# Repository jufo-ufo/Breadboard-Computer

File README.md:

# Breadboard-Computer
Let's build a computer from ICs!

## TODO
- [X] Test out NAND vs NOT, AND, OR
- [X] Write specification for V0.4
  - [X] Add Instructionset to "Handbuch"
  - [X] Rework Interrupts
  - [X] I/O specification
  - [X] Update Flags
  - [X] ~~Insert test results~~
- [X] Get familiar with ~~EAGLE/Target3001~~ Kicad/Logisim
- [ ] Build circuit designs

| Part                  | Logic | Schematic | Layout | Breadboard | Etching | Soldering | Etcher | Documenation | Comment
|-----------------------|-------|-----------|--------|------------|---------|-----------|--------|--------------|---------
| Bank                  | [X]   | [X]       | [ ]    | [ ]        | [ ]     | [ ]       |        | [ ]          | 
| Bank\_controller      | [X]   | [X]       | [ ]    | [ ]        | [ ]     | [ ]       |        | [ ]          |
| Memory                | [X]   | [X]       | [X]    | [ ]        | [ ]     | [ ]       |        | [ ]          | 
| Register\_File        | [X]   | [X]       | [ ]    | [ ]        | [ ]     | [ ]       |        | [ ]          | 
| ALU                   | [X]   | [X]       | [ ]    | [ ]        | [ ]     | [ ]       |        | [ ]          | 
| IV\_Storage           | [X]   | [ ]       | [ ]    | [ ]        | [ ]     | [ ]       |        | [ ]          | 
| Interrupt\_Controller | [ ]   | [ ]       | [ ]    | [ ]        | [ ]     | [ ]       |        | [ ]          | 
| Timer                 | [X]   | [ ]       | [ ]    | [ ]        | [ ]     | [ ]       |        | [ ]          | 
| Freq\_Counter         | [X]   | [ ]       | [ ]    | [ ]        | [ ]     | [ ]       |        | [ ]          | 
| Instruction\_Decoder  | [X]   | [ ]       | [ ]    | [ ]        | [ ]     | [ ]       |        | [ ]          | 
| IO\_Controller        | [ ]   | [ ]       | [ ]    | [ ]        | [ ]     | [ ]       |        | [ ]          | 
| Activation\_Module    | [X]   | [X]       | [X]    | [X]        | [ ] x7  | [ ] x7    |        | [ ]          | 
| Dual\_Register        | [X]   | [X]       | [X]    | [X]        | [ ] x2  | [ ] x2    |        | [ ]          | Replacement for BID-Regiser and IR
https://www.youtube.com/watch?v=9aUsTlBjspE

## TODO for Presentation
| Module               | Logic | Schematic | Layout | Breaboard | DIY Etching | Soldering | Comment
|----------------------|-------|-----------|--------|-----------|-------------|-----------|--------
| Activation Module x4 | [X]   | [X]       | [X]    |           |             | [ ]       |
| Register File        | [X]   | [X]       | [ ]    |           |             | [ ]       |
| ALU                  | [X]   | [ ]       |        | [ ]       |             |           |
| Dual Register        | [X]   | [X]       | [X]    |           | [X]         | [ ]       |
| Memory               | [X]   | [X]       | [X]    |           |             | [ ]       |
| Instruction Decoader | [X]   |           |        | [ ]       |             |           | No Schematic need, due unstable design
| IO-Controller        | [X]   |           |        | [ ]       |             |           | No Schematic need, has to be build spontainiously

## Was macht unseren Computer besonders?

- Modular: Die Funktionialiät des Computer kann erweitern werden indem neues einfach eingesteckt wird
- 2 Bus-Architektur: Efficenter
- IO-System sehr vielfältig: bis zu 2^16 IO-Geräte
- Wäre der Laufzeit anpassbares Instruktions Satz (kommt noch)
- Keine Softwareverwaltes Berechtigungs System: Supervisor/Usermode

=> Sehr einfache Anpassbarkeit und Optimierung auf Verschieden Zenarien

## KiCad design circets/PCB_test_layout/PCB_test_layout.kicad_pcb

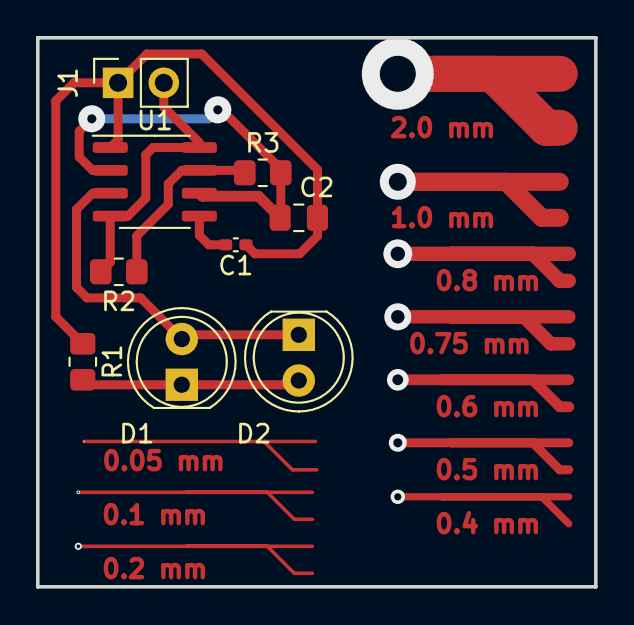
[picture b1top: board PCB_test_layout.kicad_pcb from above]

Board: 2 copper layers, 31.0 x 30.5 mm, 9 parts (0 on the bottom side), 7 nets.

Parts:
C1: 10n; C_0402_1005Metric_Pad0.74x0.62mm_HandSolder
C2: 10µ; C_0805_2012Metric_Pad1.18x1.45mm_HandSolder
D1, D2: LED; LED_D5.0mm
J1: Conn_01x02_Male; PinSocket_1x02_P2.54mm_Vertical
R1: 220; R_0805_2012Metric_Pad1.20x1.40mm_HandSolder
R2: 40k; R_0805_2012Metric_Pad1.20x1.40mm_HandSolder
R3: 10k; R_0805_2012Metric_Pad1.20x1.40mm_HandSolder
U1: NE555D; SOIC-8_3.9x4.9mm_P1.27mm

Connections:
+5V: J1.2, R2.2, U1.4 (R), U1.8 (VCC)
GND: C1.1, C2.2, J1.1, R1.1, U1.1 (GND)
unnamed: C1.2, U1.5 (CV)
unnamed: C2.1, R3.2, U1.2 (TR), U1.6 (THR)
unnamed: D1.1 (K), D2.2 (A), R1.2
unnamed: D1.2 (A), D2.1 (K), U1.3 (Q)
unnamed: R2.1, R3.1, U1.7 (DIS)

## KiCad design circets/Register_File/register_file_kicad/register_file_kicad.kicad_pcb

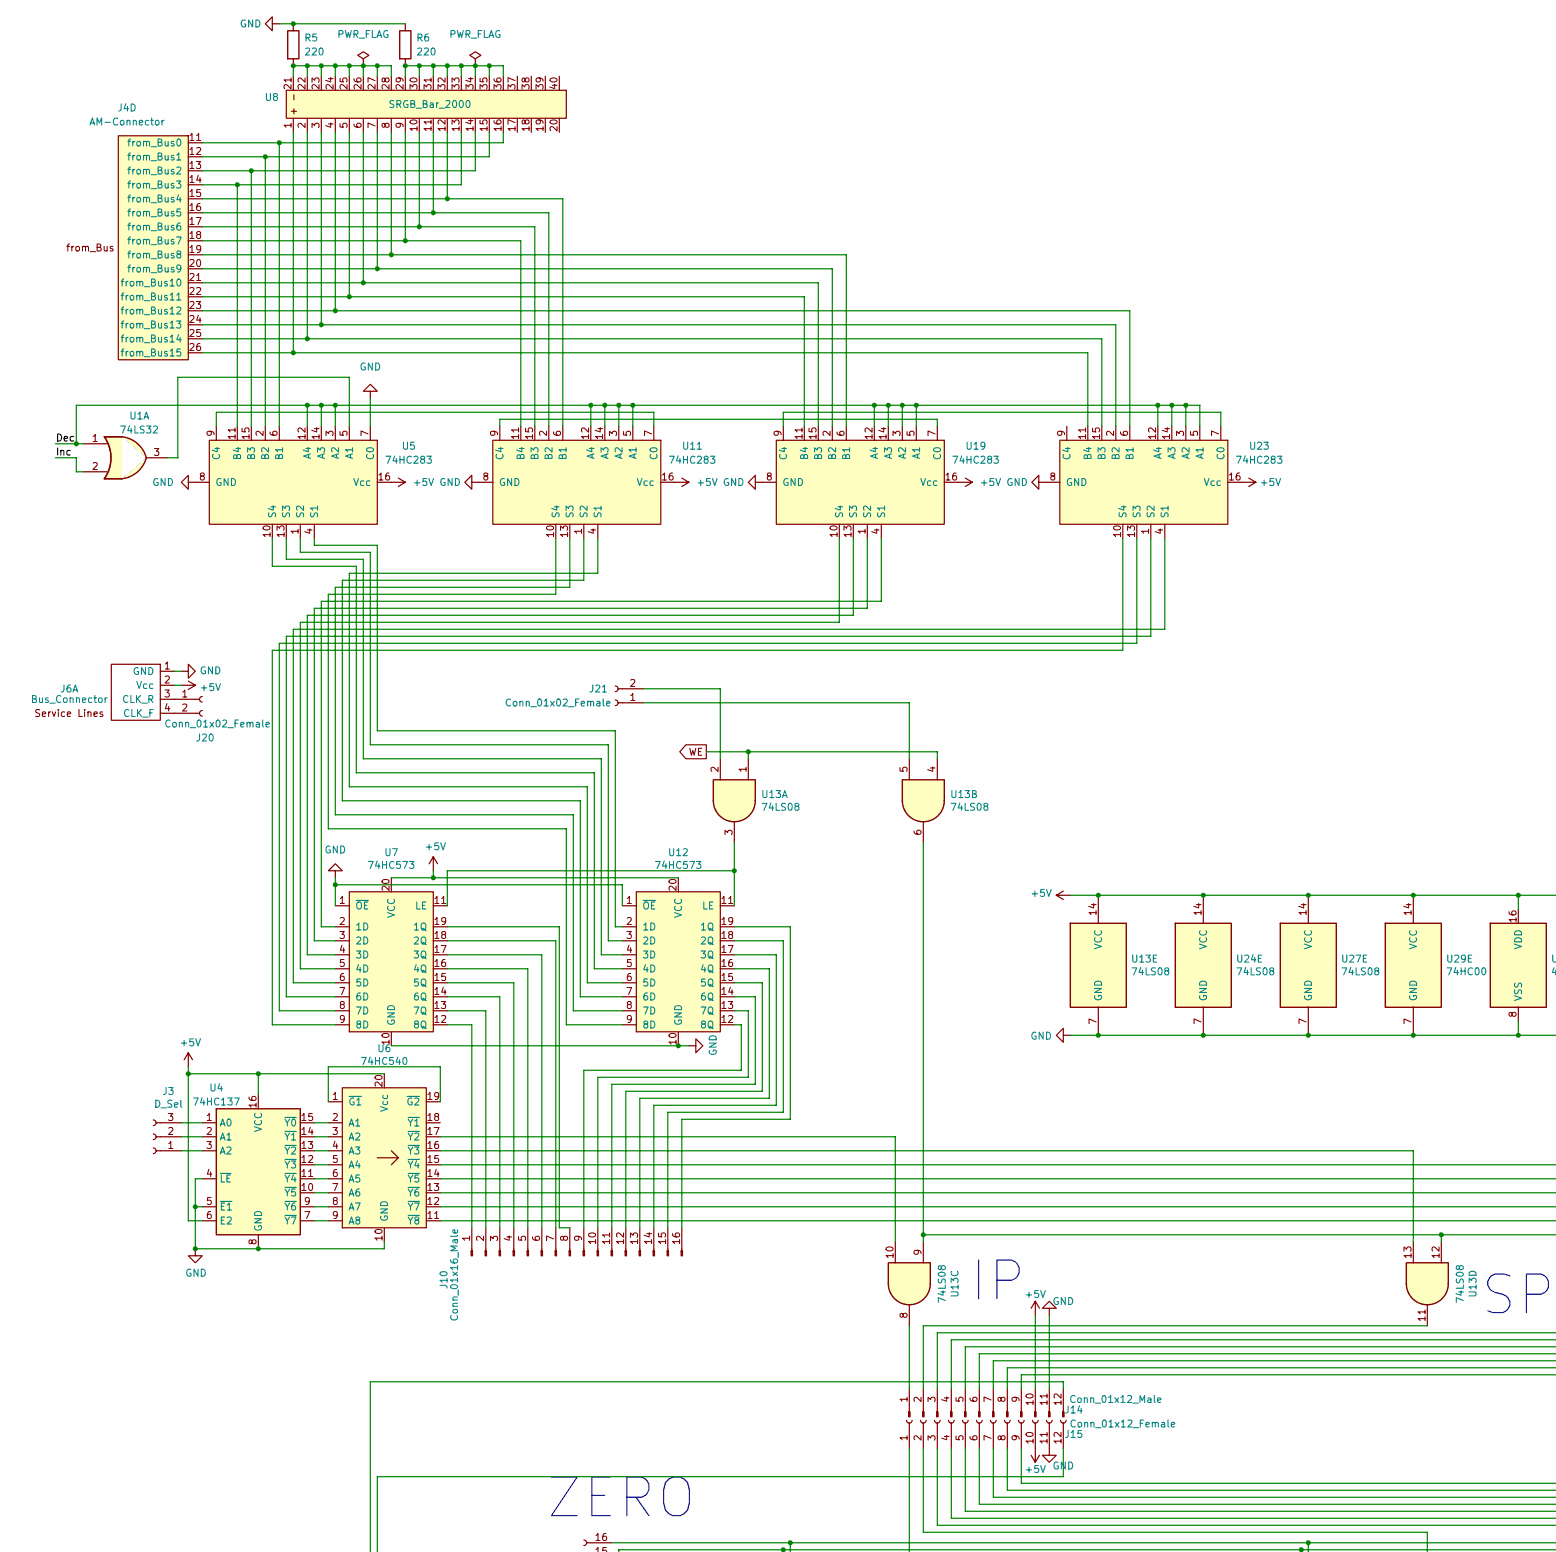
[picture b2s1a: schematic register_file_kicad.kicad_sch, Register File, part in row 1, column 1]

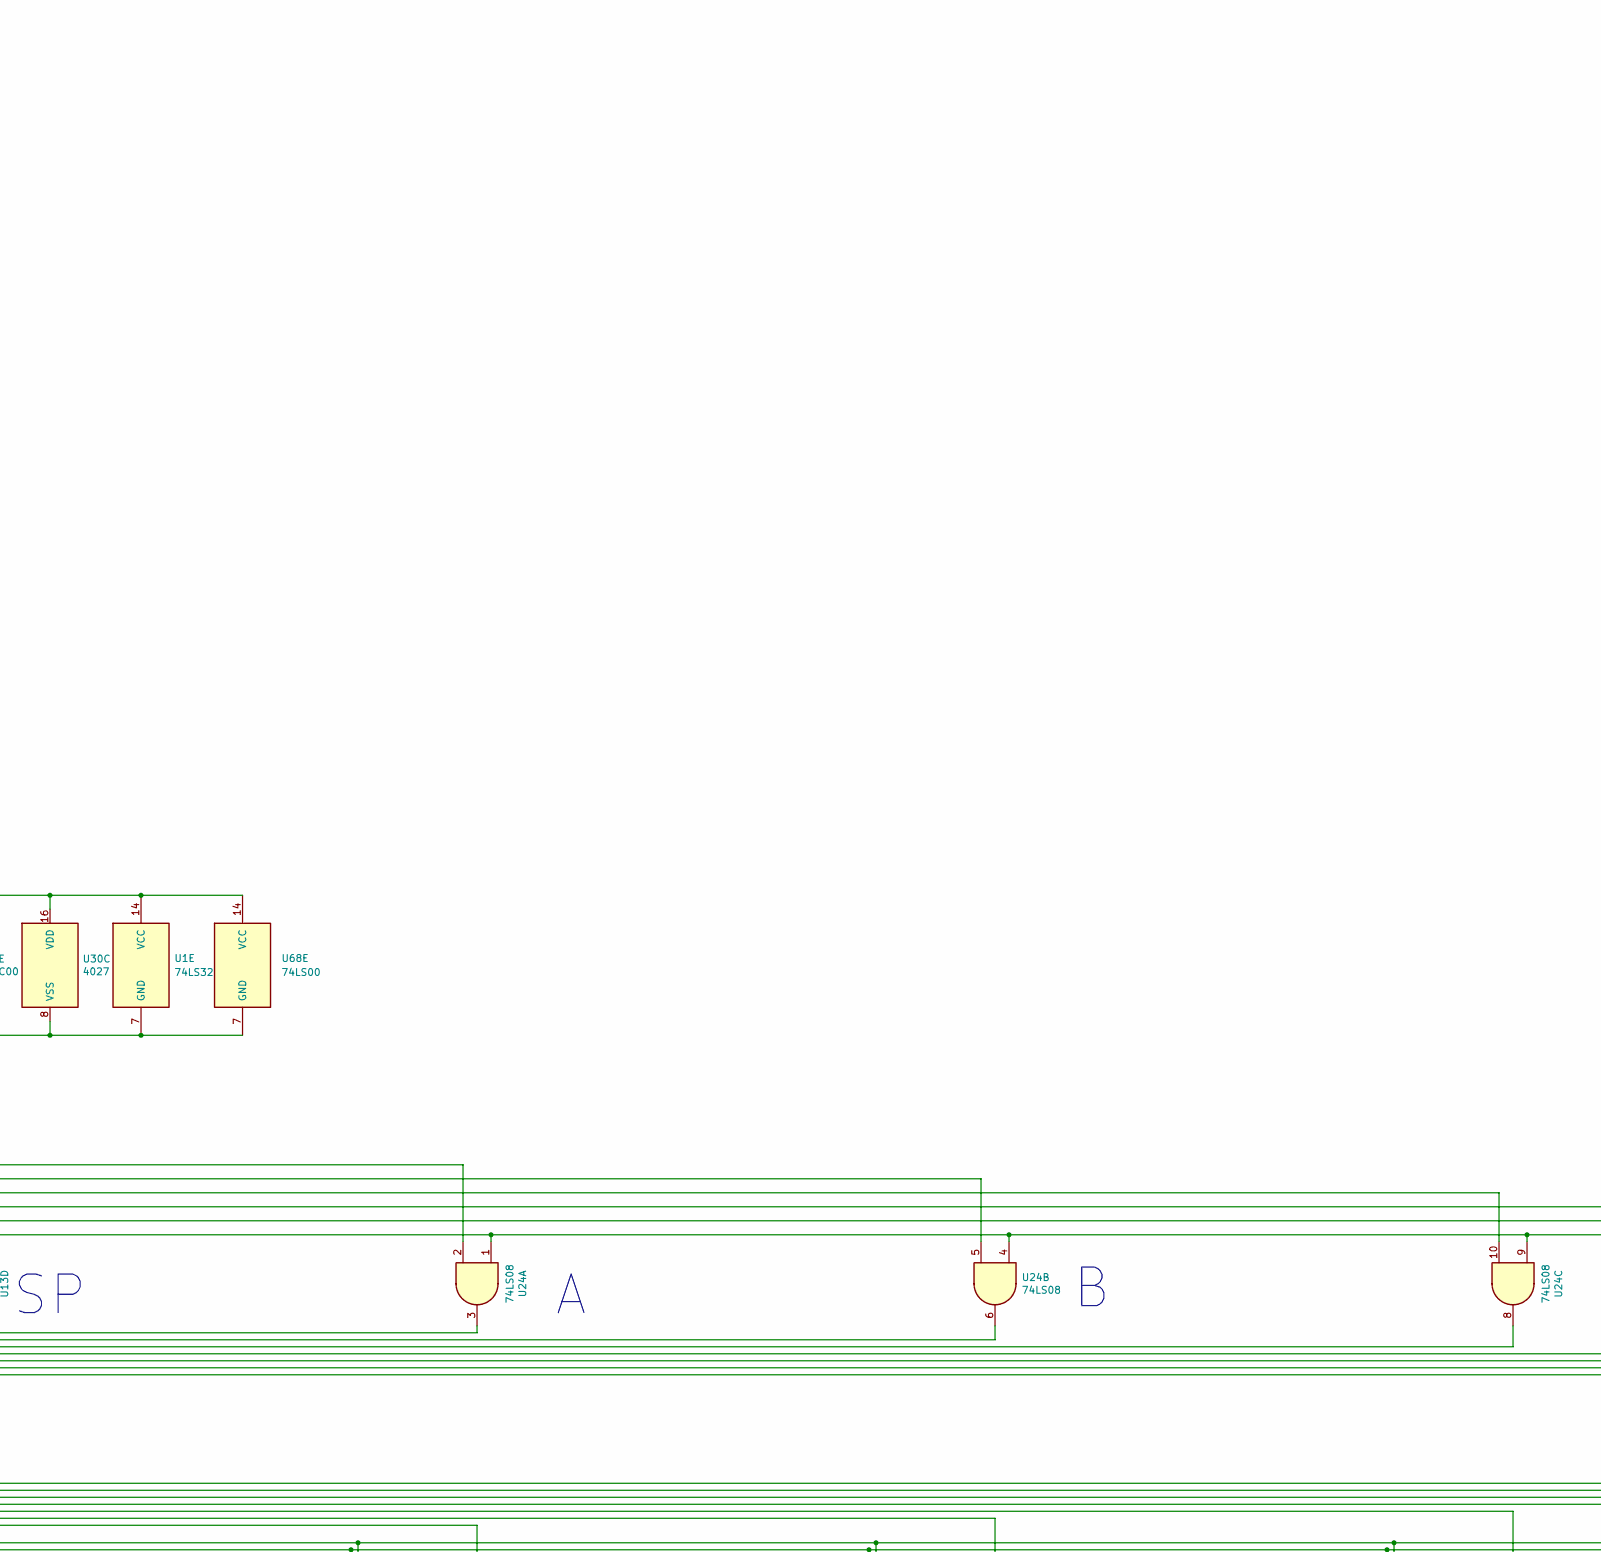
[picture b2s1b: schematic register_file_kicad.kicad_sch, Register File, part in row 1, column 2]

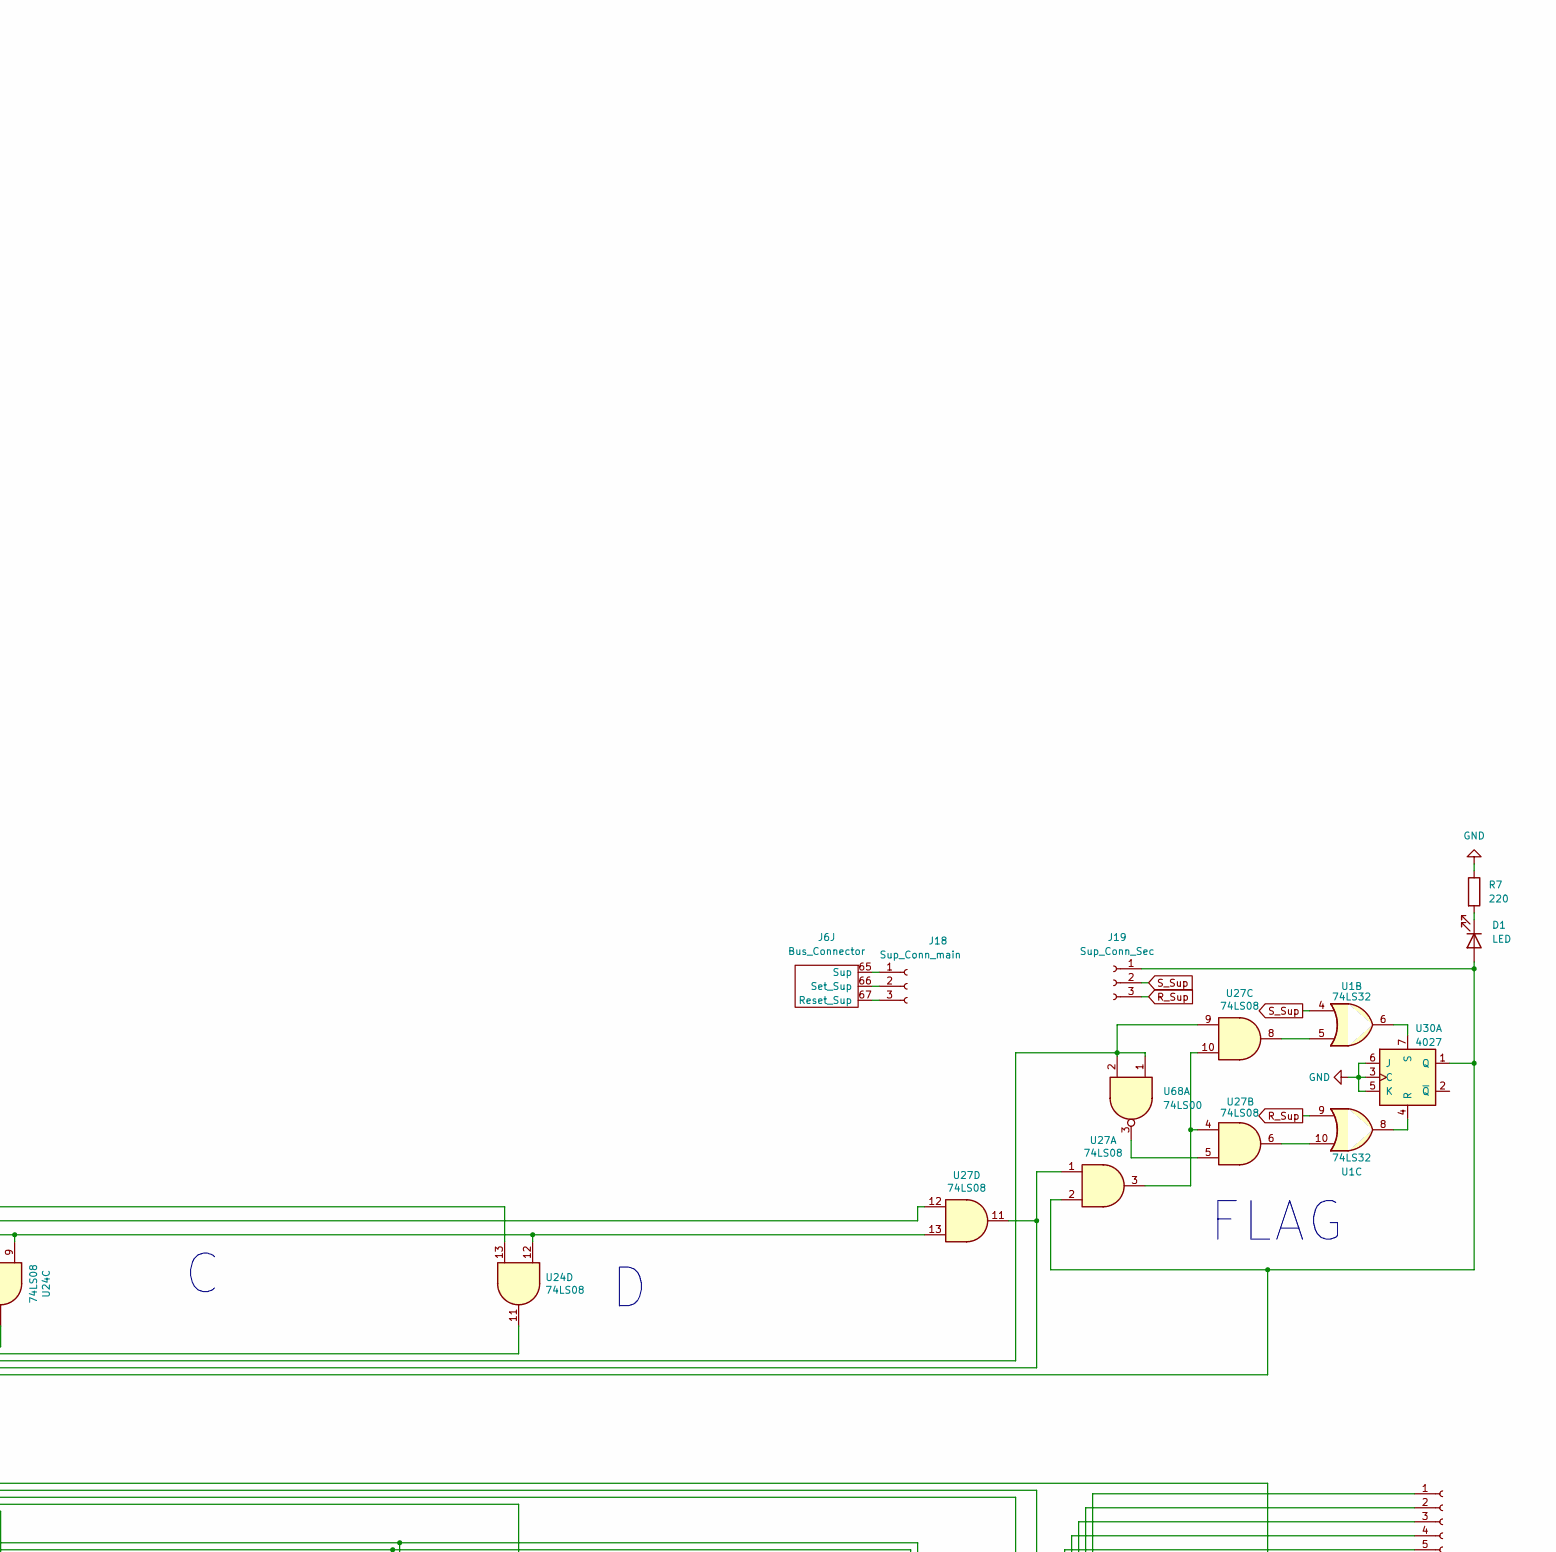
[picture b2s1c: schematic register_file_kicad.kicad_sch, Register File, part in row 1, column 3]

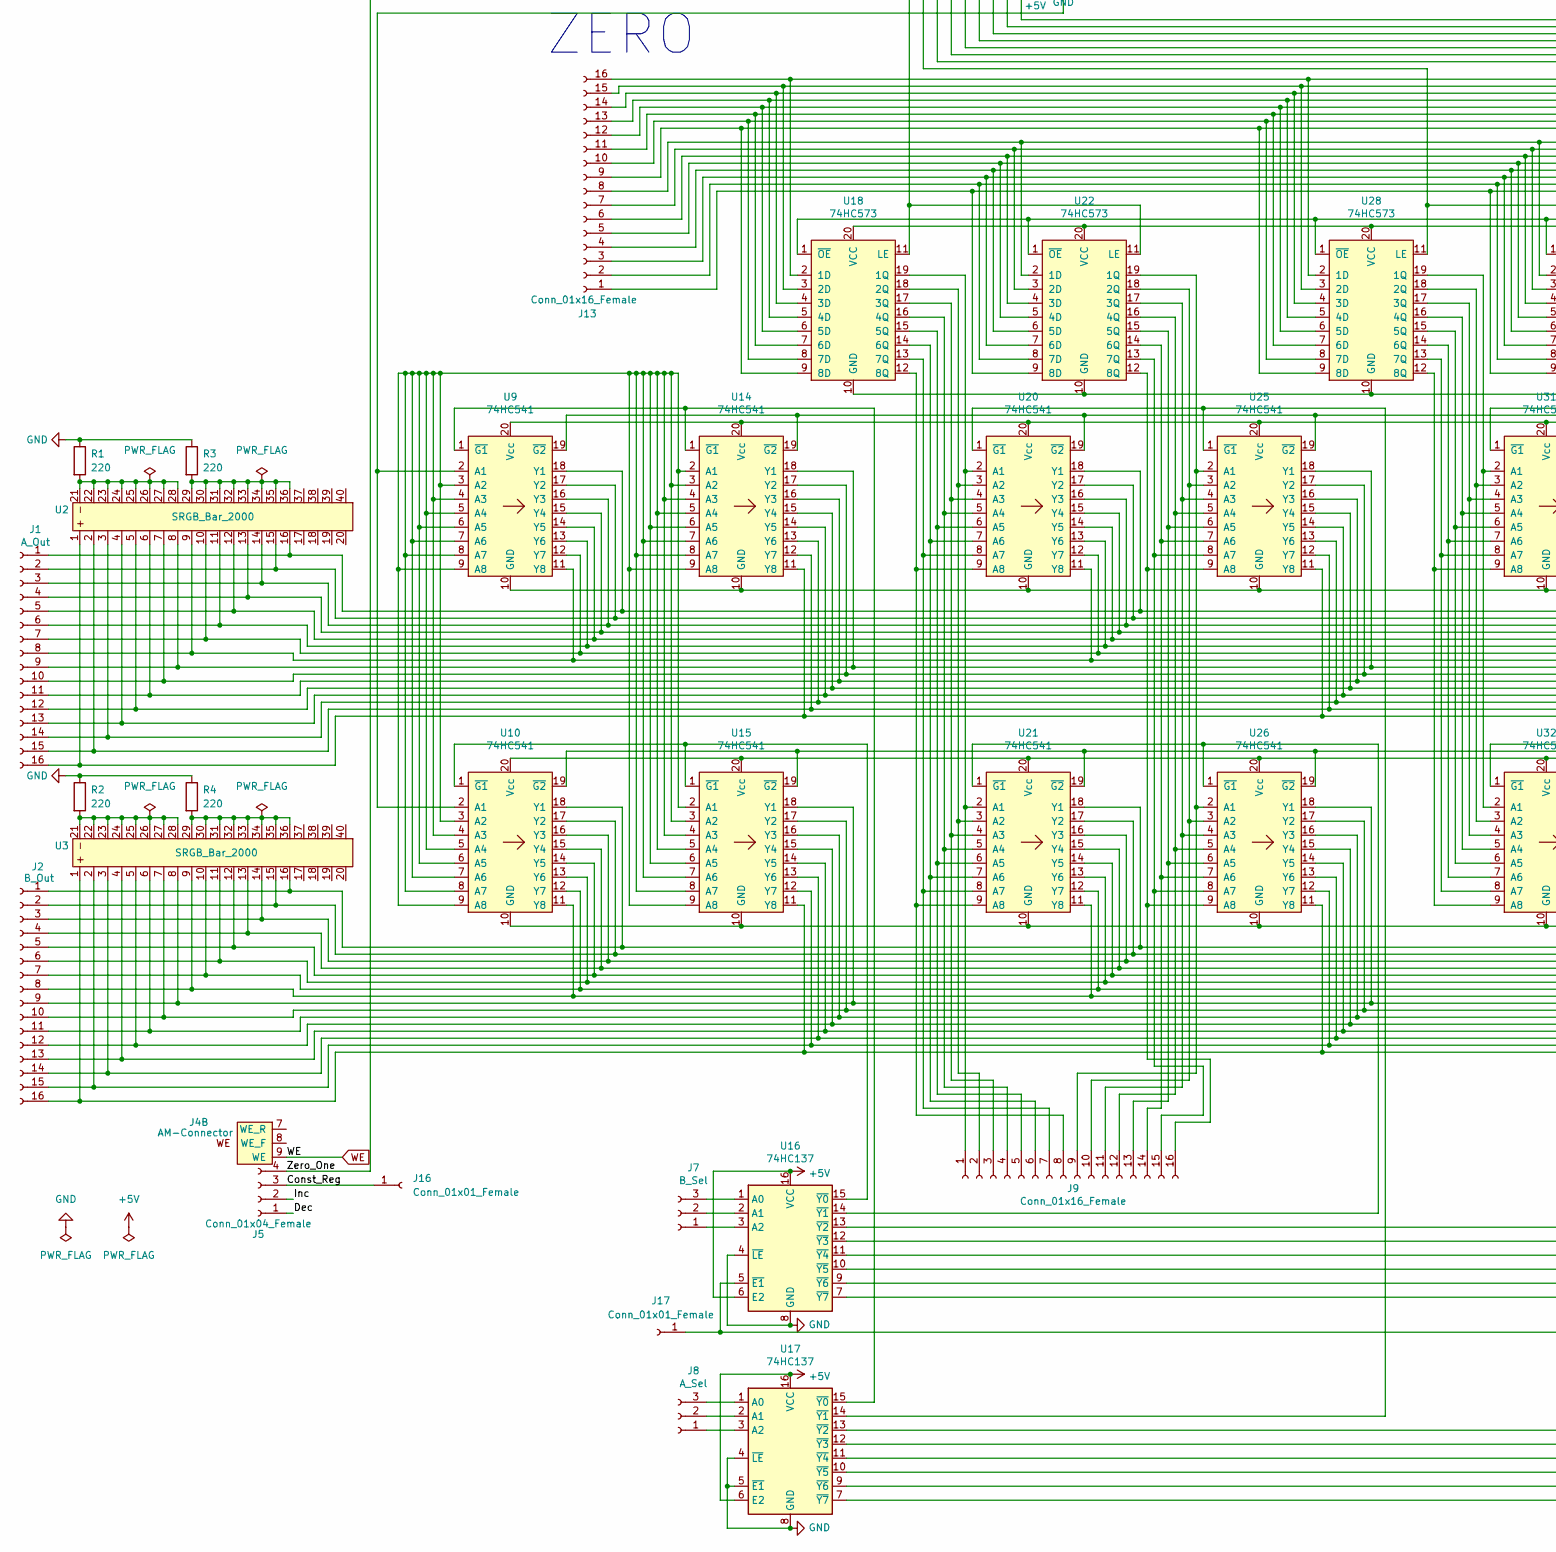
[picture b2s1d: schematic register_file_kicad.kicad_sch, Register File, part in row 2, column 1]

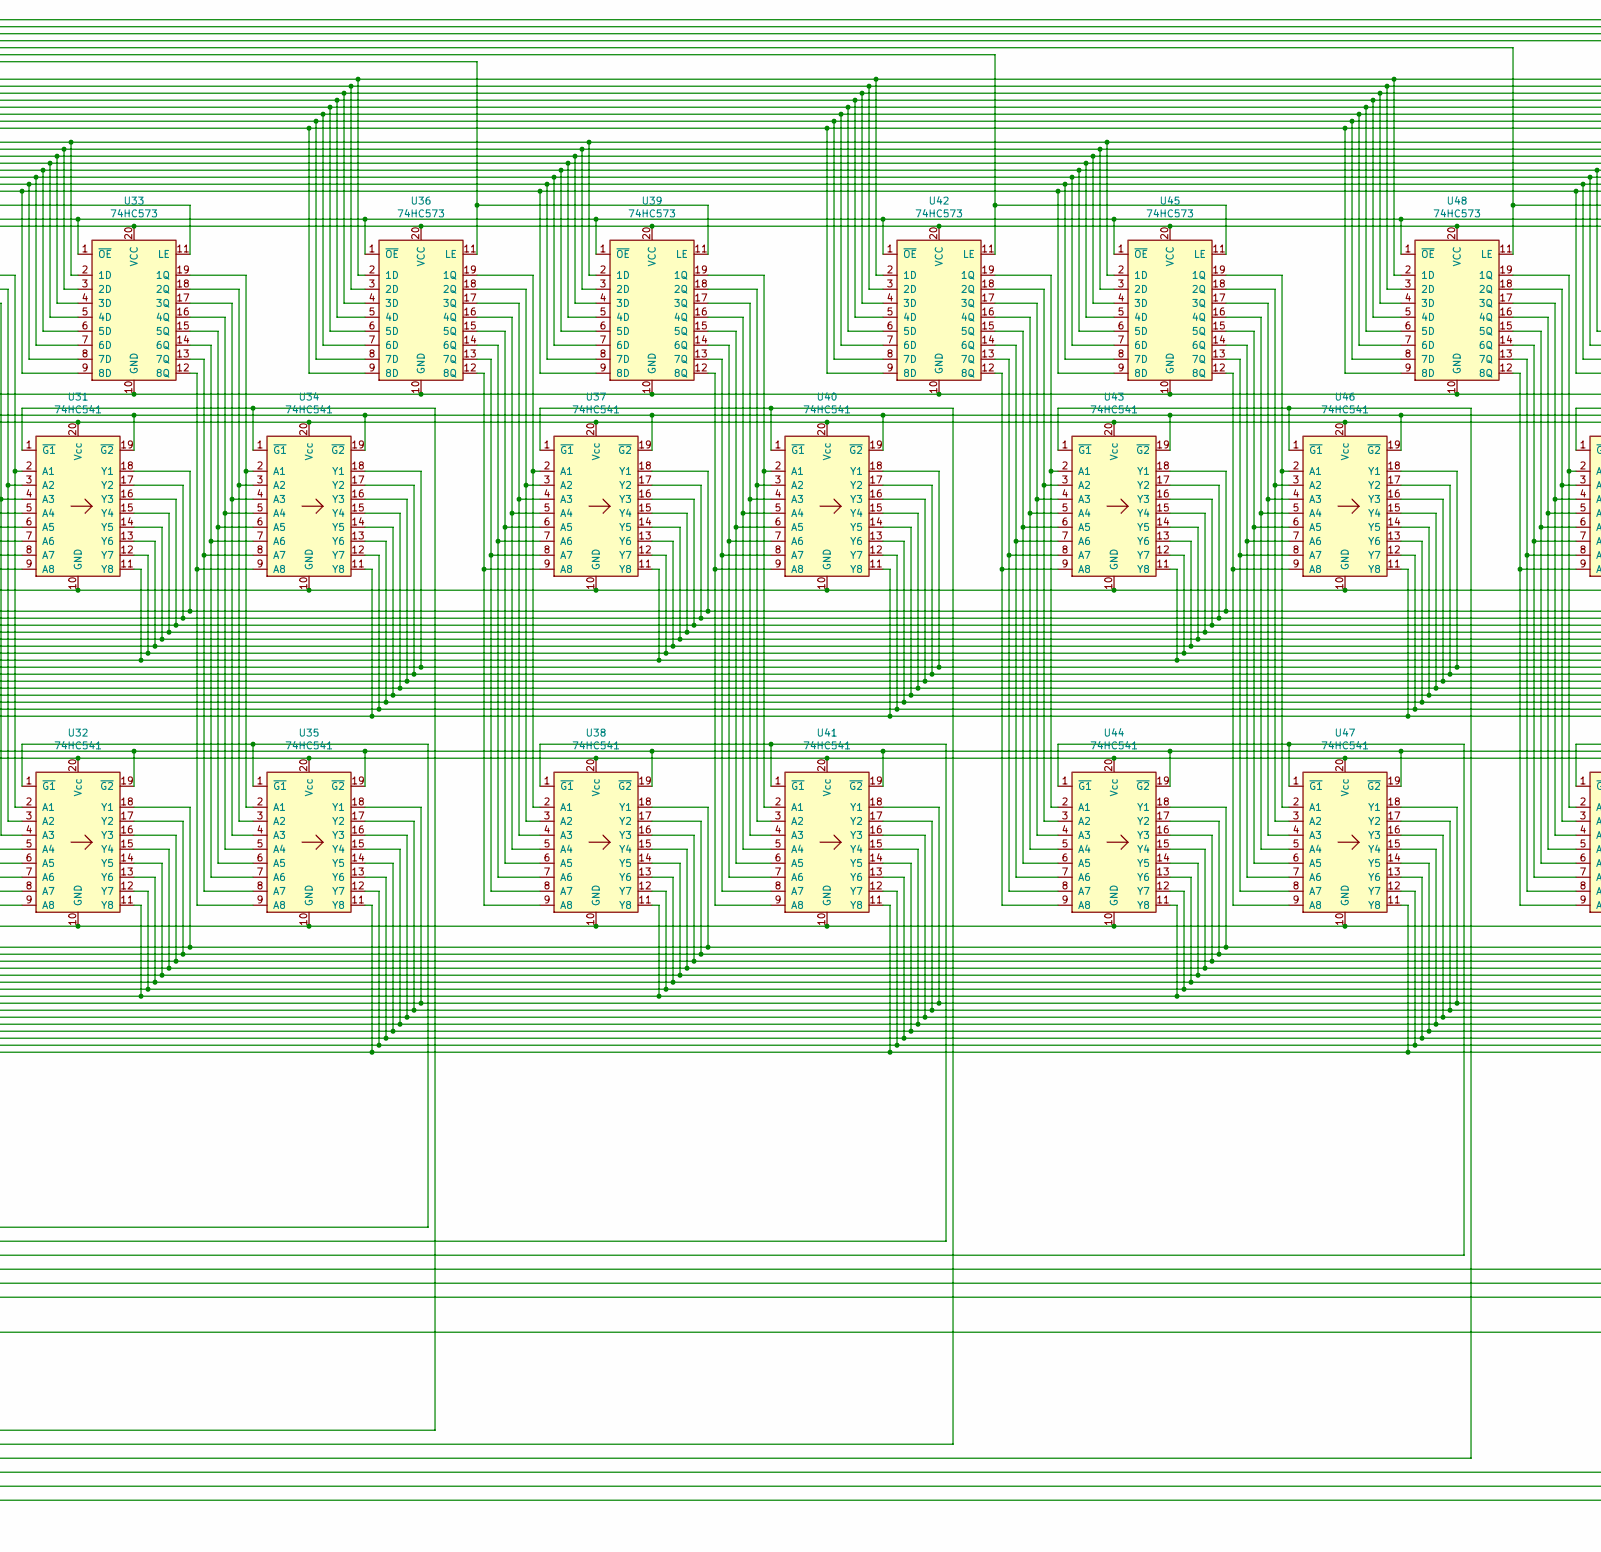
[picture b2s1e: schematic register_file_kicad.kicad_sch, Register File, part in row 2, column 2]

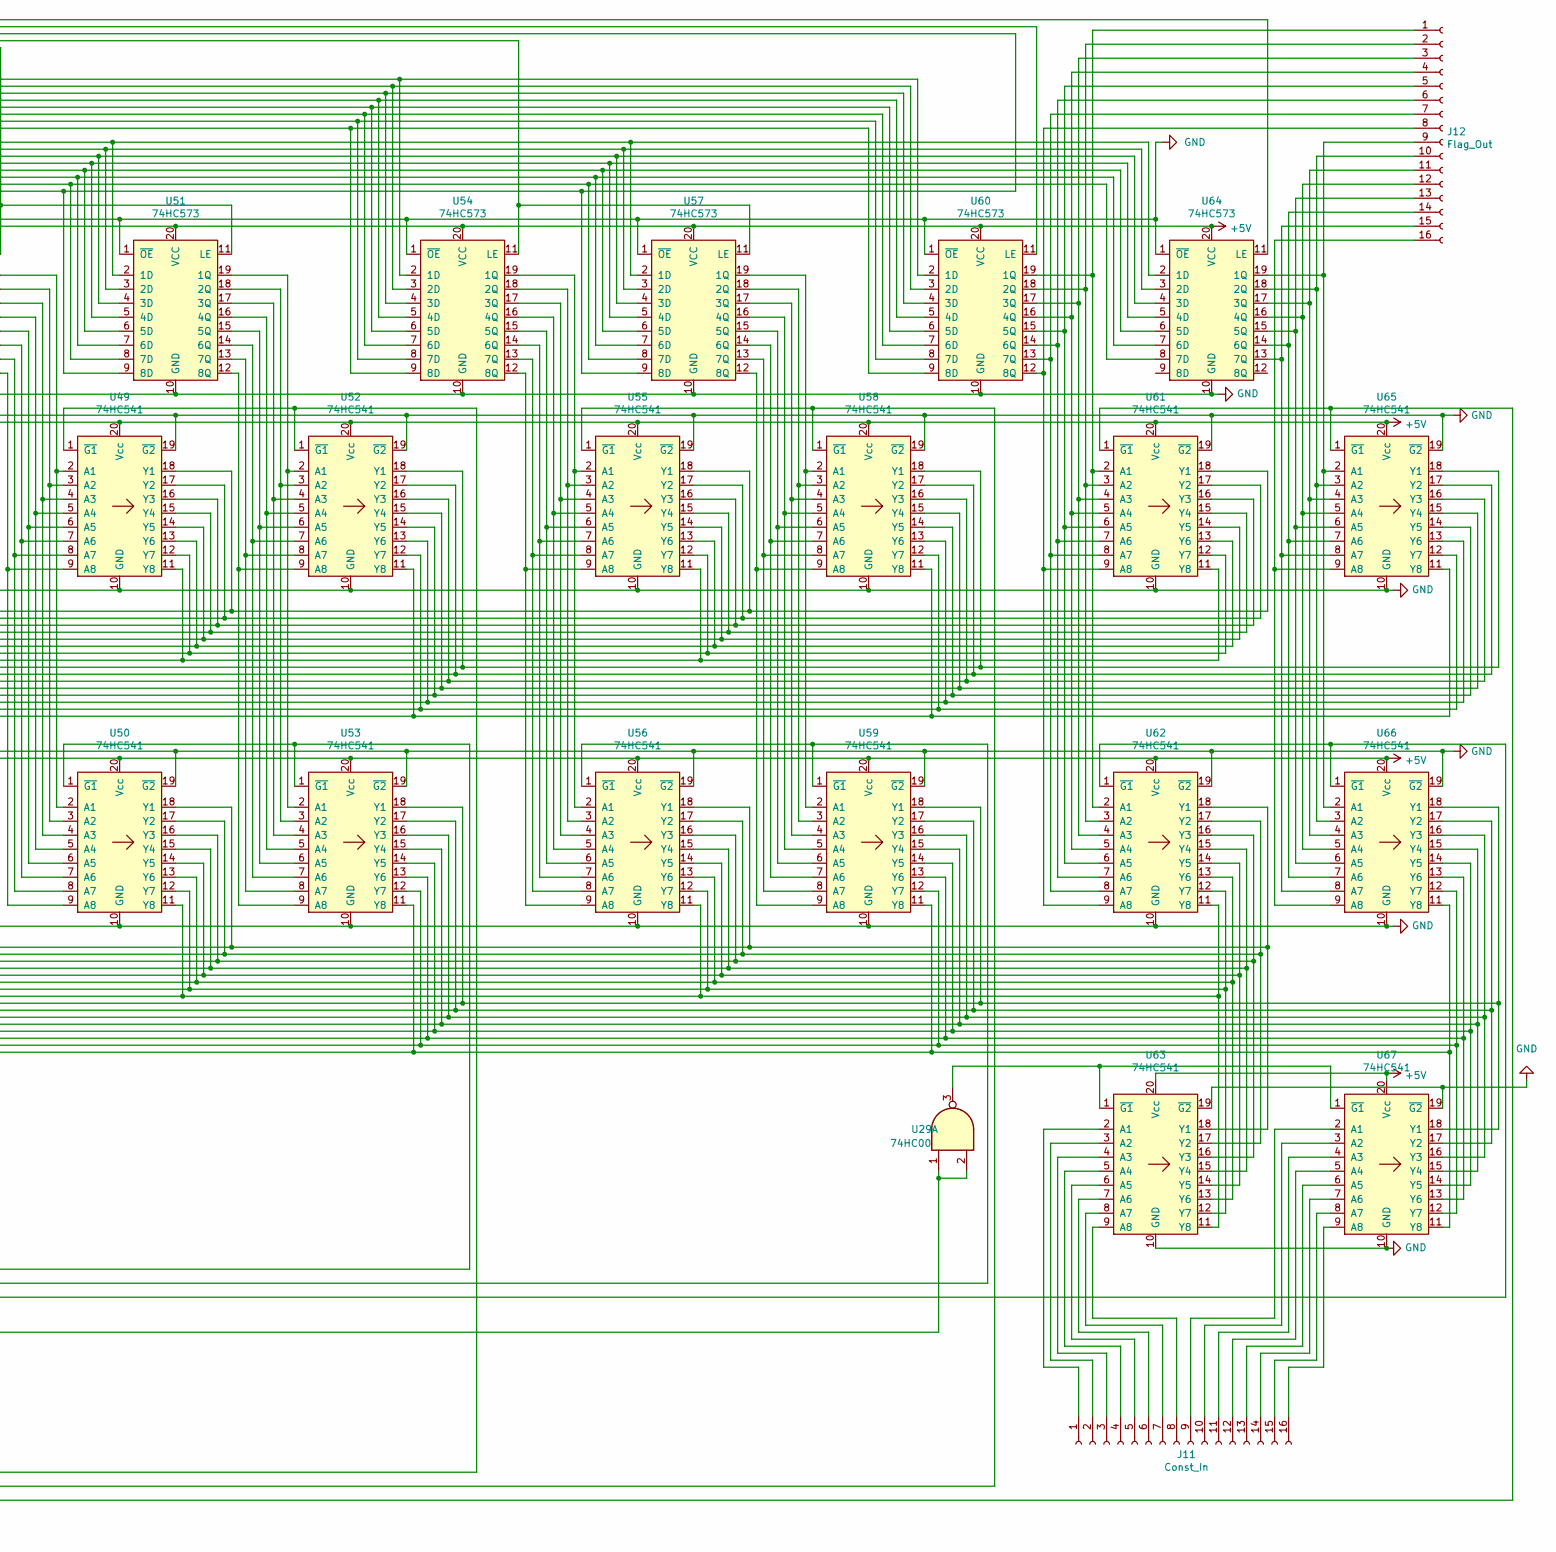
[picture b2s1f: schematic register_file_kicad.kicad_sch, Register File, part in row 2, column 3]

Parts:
D1: LED; LED_D5.0mm
J1: A_Out; PinHeader_1x16_P2.54mm_Vertical
J2: B_Out; PinHeader_1x16_P2.54mm_Vertical
J3: D_Sel; PinSocket_1x03_P2.54mm_Horizontal
J4: AM-Connector; PinHeader_1x42_P2.54mm_Horizontal
J5: Conn_01x04_Female; PinHeader_1x04_P2.54mm_Horizontal
J6: Bus_Connector; PinHeader_1x78_P2.54mm_Horizontal
J7: B_Sel; PinHeader_1x03_P2.54mm_Horizontal
J8: A_Sel; PinHeader_1x03_P2.54mm_Horizontal
J9, J13: Conn_01x16_Female; PinSocket_1x16_P2.54mm_Vertical
J10: Conn_01x16_Male; PinSocket_1x16_P2.54mm_Vertical
J11: Const_In; PinHeader_1x16_P2.54mm_Horizontal
J12: Flag_Out; PinHeader_1x16_P2.54mm_Horizontal
J14: Conn_01x12_Male; PinSocket_1x12_P2.54mm_Vertical
J15: Conn_01x12_Female; PinSocket_1x12_P2.54mm_Vertical
J16, J17: Conn_01x01_Female; PinSocket_1x01_P2.54mm_Vertical
J18: Sup_Conn_main; PinSocket_1x03_P2.54mm_Horizontal
J19: Sup_Conn_Sec; PinSocket_1x03_P2.54mm_Horizontal
J20, J21: Conn_01x02_Female; PinSocket_1x02_P2.54mm_Vertical
R1, R2, R3, R4, R5, R6, R7: 220; R_Axial_DIN0309_L9.0mm_D3.2mm_P5.08mm_Vertical
U1: 74LS32; DIP-14_W7.62mm_Socket
U2, U3, U8: SRGB_Bar_2000; SRGB_2000
U4, U16, U17: 74HC137; DIP-16_W7.62mm_Socket
U5, U11, U19, U23: 74HC283; DIP-16_W7.62mm_Socket
U6: 74HC540; DIP-20_W7.62mm_Socket
U7, U12, U18, U22, U28, U33, U36, U39, U42, U45, U48, U51, U54, U57, U60, U64: 74HC573; DIP-20_W7.62mm_Socket
U9, U10: 74HC541; SO-20_5.3x12.6mm_P1.27mm
U13, U24, U27: 74LS08; DIP-14_W7.62mm_Socket
U14, U15, U20, U21, U25, U26, U31, U32, U34, U35, U37, U38, U40, U41, U43, U44, U46, U47, U49, U50, U52, U53, U55, U56, U58, U59, U61, U62, U63, U65, U66, U67: 74HC541; SO-20_12.8x7.5mm_P1.27mm
U29: 74HC00; DIP-14_W7.62mm_Socket
U30: 4027; DIP-16_W7.62mm_Socket
U68: 74LS00; DIP-14_W7.62mm_Socket

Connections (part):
+5V: J6.2 (Vcc), J14.10, J15.10, U1.14 (VCC), U4.6 (E2), U4.16 (VCC), U5.16 (Vcc), U6.20 (Vcc), U7.20 (VCC), U9.20 (Vcc), U10.20 (Vcc), U11.16 (Vcc), U12.20 (VCC), U13.14 (VCC), U14.20 (Vcc), U15.20 (Vcc), U16.6 (E2), U16.16 (VCC), U17.6 (E2), U17.16 (VCC), U18.20 (VCC), U19.16 (Vcc), U20.20 (Vcc), U21.20 (Vcc), U22.20 (VCC), U23.16 (Vcc), U24.14 (VCC), U25.20 (Vcc), U26.20 (Vcc), U27.14 (VCC), U28.20 (VCC), U29.14 (VCC), U30.16 (VDD), U31.20 (Vcc), U32.20 (Vcc), U33.20 (VCC), U34.20 (Vcc), U35.20 (Vcc), U36.20 (VCC), U37.20 (Vcc), U38.20 (Vcc), U39.20 (VCC), U40.20 (Vcc), U41.20 (Vcc), U42.20 (VCC), U43.20 (Vcc), U44.20 (Vcc), U45.20 (VCC), U46.20 (Vcc), U47.20 (Vcc), U48.20 (VCC), U49.20 (Vcc), U50.20 (Vcc), U51.20 (VCC), U52.20 (Vcc), U53.20 (Vcc), U54.20 (VCC), U55.20 (Vcc), U56.20 (Vcc), U57.20 (VCC), U58.20 (Vcc), U59.20 (Vcc), U60.20 (VCC), U61.20 (Vcc), U62.20 (Vcc), U63.20 (Vcc), U64.20 (VCC), U65.20 (Vcc), U66.20 (Vcc), U67.20 (Vcc), U68.14 (VCC)
/Const_Reg: J5.3, J16.1
/Dec: J5.1, U1.1, U5.3 (A2), U5.12 (A4), U5.14 (A3), U11.3 (A2), U11.5 (A1), U11.12 (A4), U11.14 (A3), U19.3 (A2), U19.5 (A1), U19.12 (A4), U19.14 (A3), U23.3 (A2), U23.5 (A1), U23.12 (A4), U23.14 (A3)
/Inc: J5.2, U1.2
/Zero_One: J5.4, J14.12
GND: J6.1 (GND), J14.11, J15.11, R1.1, R2.1, R3.1, R4.1, R5.1, R6.1, R7.1, U1.7 (GND), U4.4 (~LE), U4.5 (~E1), U4.8 (GND), U5.7 (C0), U5.8 (GND), U6.10 (GND), U7.1 (~OE), U7.10 (GND), U9.10 (GND), U9.19 (~G2), U10.10 (GND), U10.19 (~G2), U11.8 (GND), U12.1 (~OE), U12.10 (GND), U13.7 (GND), U14.10 (GND), U14.19 (~G2), U15.10 (GND), U15.19 (~G2), U16.4 (~LE), U16.8 (GND), U17.4 (~LE), U17.5 (~E1), U17.8 (GND), U18.1 (~OE), U18.10 (GND), U19.8 (GND), U20.10 (GND), U20.19 (~G2), U21.10 (GND), U21.19 (~G2), U22.1 (~OE), U22.10 (GND), U23.8 (GND), U24.7 (GND), U25.10 (GND), U25.19 (~G2), U26.10 (GND), U26.19 (~G2), U27.7 (GND), U28.1 (~OE), U28.10 (GND), U29.7 (GND), U30.3 (C), U30.5 (K), U30.6 (J), U30.8 (VSS), U31.10 (GND), U31.19 (~G2), U32.10 (GND), U32.19 (~G2), U33.1 (~OE), U33.10 (GND), U34.10 (GND), U34.19 (~G2), U35.10 (GND), U35.19 (~G2), U36.1 (~OE), U36.10 (GND), U37.10 (GND), U37.19 (~G2), U38.10 (GND), U38.19 (~G2), U39.1 (~OE), U39.10 (GND), U40.10 (GND), U40.19 (~G2), U41.10 (GND), U41.19 (~G2), U42.1 (~OE), U42.10 (GND), U43.10 (GND), U43.19 (~G2), U44.10 (GND)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
unnamed: D1.1 (K), R7.2
unnamed: D1.2 (A), J14.9, J19.1, U27.2, U30.1 (Q)
unnamed: J1.1, U2.16, U9.18 (Y1), U20.18 (Y1), U31.18 (Y1), U37.18 (Y1), U43.18 (Y1), U49.18 (Y1), U55.18 (Y1), U61.18 (Y1)
unnamed: J1.2, U2.15, U9.17 (Y2), U20.17 (Y2), U31.17 (Y2), U37.17 (Y2), U43.17 (Y2), U49.17 (Y2), U55.17 (Y2), U61.17 (Y2)
unnamed: J1.3, U2.14, U9.16 (Y3), U20.16 (Y3), U31.16 (Y3), U37.16 (Y3), U43.16 (Y3), U49.16 (Y3), U55.16 (Y3), U61.16 (Y3)
unnamed: J1.4, U2.13, U9.15 (Y4), U20.15 (Y4), U31.15 (Y4), U37.15 (Y4), U43.15 (Y4), U49.15 (Y4), U55.15 (Y4), U61.15 (Y4)
unnamed: J1.5, U2.12, U9.14 (Y5), U20.14 (Y5), U31.14 (Y5), U37.14 (Y5), U43.14 (Y5), U49.14 (Y5), U55.14 (Y5), U61.14 (Y5)
unnamed: J1.6, U2.11, U9.13 (Y6), U20.13 (Y6), U31.13 (Y6), U37.13 (Y6), U43.13 (Y6), U49.13 (Y6), U55.13 (Y6), U61.13 (Y6)
unnamed: J1.7, U2.10, U9.12 (Y7), U20.12 (Y7), U31.12 (Y7), U37.12 (Y7), U43.12 (Y7), U49.12 (Y7), U55.12 (Y7), U61.12 (Y7)
unnamed: J1.8, U2.9, U9.11 (Y8), U20.11 (Y8), U31.11 (Y8), U37.11 (Y8), U43.11 (Y8), U49.11 (Y8), U55.11 (Y8), U61.11 (Y8)
unnamed: J1.9, U2.8, U14.18 (Y1), U25.18 (Y1), U34.18 (Y1), U40.18 (Y1), U46.18 (Y1), U52.18 (Y1), U58.18 (Y1), U65.18 (Y1)
unnamed: J1.10, U2.7, U14.17 (Y2), U25.17 (Y2), U34.17 (Y2), U40.17 (Y2), U46.17 (Y2), U52.17 (Y2), U58.17 (Y2), U65.17 (Y2)
unnamed: J1.11, U2.6, U14.16 (Y3), U25.16 (Y3), U34.16 (Y3), U40.16 (Y3), U46.16 (Y3), U52.16 (Y3), U58.16 (Y3), U65.16 (Y3)
unnamed: J1.12, U2.5, U14.15 (Y4), U25.15 (Y4), U34.15 (Y4), U40.15 (Y4), U46.15 (Y4), U52.15 (Y4), U58.15 (Y4), U65.15 (Y4)
unnamed: J1.13, U2.4, U14.14 (Y5), U25.14 (Y5), U34.14 (Y5), U40.14 (Y5), U46.14 (Y5), U52.14 (Y5), U58.14 (Y5), U65.14 (Y5)
unnamed: J1.14, U2.3, U14.13 (Y6), U25.13 (Y6), U34.13 (Y6), U40.13 (Y6), U46.13 (Y6), U52.13 (Y6), U58.13 (Y6), U65.13 (Y6)
unnamed: J1.15, U2.2, U14.12 (Y7), U25.12 (Y7), U34.12 (Y7), U40.12 (Y7), U46.12 (Y7), U52.12 (Y7), U58.12 (Y7), U65.12 (Y7)
unnamed: J1.16, U2.1, U14.11 (Y8), U25.11 (Y8), U34.11 (Y8), U40.11 (Y8), U46.11 (Y8), U52.11 (Y8), U58.11 (Y8), U65.11 (Y8)
unnamed: J2.1, U3.16, U10.18 (Y1), U21.18 (Y1), U32.18 (Y1), U38.18 (Y1), U44.18 (Y1), U50.18 (Y1), U56.18 (Y1), U62.18 (Y1), U63.18 (Y1)
unnamed: J2.2, U3.15, U10.17 (Y2), U21.17 (Y2), U32.17 (Y2), U38.17 (Y2), U44.17 (Y2), U50.17 (Y2), U56.17 (Y2), U62.17 (Y2), U63.17 (Y2)
unnamed: J2.3, U3.14, U10.16 (Y3), U21.16 (Y3), U32.16 (Y3), U38.16 (Y3), U44.16 (Y3), U50.16 (Y3), U56.16 (Y3), U62.16 (Y3), U63.16 (Y3)
unnamed: J2.4, U3.13, U10.15 (Y4), U21.15 (Y4), U32.15 (Y4), U38.15 (Y4), U44.15 (Y4), U50.15 (Y4), U56.15 (Y4), U62.15 (Y4), U63.15 (Y4)
unnamed: J2.5, U3.12, U10.14 (Y5), U21.14 (Y5), U32.14 (Y5), U38.14 (Y5), U44.14 (Y5), U50.14 (Y5), U56.14 (Y5), U62.14 (Y5), U63.14 (Y5)
unnamed: J2.6, U3.11, U10.13 (Y6), U21.13 (Y6), U32.13 (Y6), U38.13 (Y6), U44.13 (Y6), U50.13 (Y6), U56.13 (Y6), U62.13 (Y6), U63.13 (Y6)
unnamed: J2.7, U3.10, U10.12 (Y7), U21.12 (Y7), U32.12 (Y7), U38.12 (Y7), U44.12 (Y7), U50.12 (Y7), U56.12 (Y7), U62.12 (Y7), U63.12 (Y7)
unnamed: J2.8, U3.9, U10.11 (Y8), U21.11 (Y8), U32.11 (Y8), U38.11 (Y8), U44.11 (Y8), U50.11 (Y8), U56.11 (Y8), U62.11 (Y8), U63.11 (Y8)
unnamed: J2.9, U3.8, U15.18 (Y1), U26.18 (Y1), U35.18 (Y1), U41.18 (Y1), U47.18 (Y1), U53.18 (Y1), U59.18 (Y1), U66.18 (Y1), U67.18 (Y1)
unnamed: J2.10, U3.7, U15.17 (Y2), U26.17 (Y2), U35.17 (Y2), U41.17 (Y2), U47.17 (Y2), U53.17 (Y2), U59.17 (Y2), U66.17 (Y2), U67.17 (Y2)
unnamed: J2.11, U3.6, U15.16 (Y3), U26.16 (Y3), U35.16 (Y3), U41.16 (Y3), U47.16 (Y3), U53.16 (Y3), U59.16 (Y3), U66.16 (Y3), U67.16 (Y3)
unnamed: J2.12, U3.5, U15.15 (Y4), U26.15 (Y4), U35.15 (Y4), U41.15 (Y4), U47.15 (Y4), U53.15 (Y4), U59.15 (Y4), U66.15 (Y4), U67.15 (Y4)
unnamed: J2.13, U3.4, U15.14 (Y5), U26.14 (Y5), U35.14 (Y5), U41.14 (Y5), U47.14 (Y5), U53.14 (Y5), U59.14 (Y5), U66.14 (Y5), U67.14 (Y5)
unnamed: J2.14, U3.3, U15.13 (Y6), U26.13 (Y6), U35.13 (Y6), U41.13 (Y6), U47.13 (Y6), U53.13 (Y6), U59.13 (Y6), U66.13 (Y6), U67.13 (Y6)
unnamed: J2.15, U3.2, U15.12 (Y7), U26.12 (Y7), U35.12 (Y7), U41.12 (Y7), U47.12 (Y7), U53.12 (Y7), U59.12 (Y7), U66.12 (Y7), U67.12 (Y7)
unnamed: J2.16, U3.1, U15.11 (Y8), U26.11 (Y8), U35.11 (Y8), U41.11 (Y8), U47.11 (Y8), U53.11 (Y8), U59.11 (Y8), U66.11 (Y8), U67.11 (Y8)
unnamed: J3.1, U4.3 (A2)
unnamed: J3.2, U4.2 (A1)
unnamed: J3.3, U4.1 (A0)
unnamed: J4.11 (from_Bus0), U5.6 (B1), U8.16
unnamed: J4.12 (from_Bus1), U5.2 (B2), U8.15
unnamed: J4.13 (from_Bus2), U5.15 (B3), U8.14
unnamed: J4.14 (from_Bus3), U5.11 (B4), U8.13
unnamed: J4.15 (from_Bus4), U8.12, U11.6 (B1)
unnamed: J4.16 (from_Bus5), U8.11, U11.2 (B2)
unnamed: J4.17 (from_Bus6), U8.10, U11.15 (B3)
unnamed: J4.18 (from_Bus7), U8.9, U11.11 (B4)
unnamed: J4.19 (from_Bus8), U8.8, U19.6 (B1)
unnamed: J4.20 (from_Bus9), U8.7, U19.2 (B2)
unnamed: J4.21 (from_Bus10), U8.6, U19.15 (B3)
unnamed: J4.22 (from_Bus11), U8.5, U19.11 (B4)
unnamed: J4.23 (from_Bus12), U8.4, U23.6 (B1)
unnamed: J4.24 (from_Bus13), U8.3, U23.2 (B2)
unnamed: J4.25 (from_Bus14), U8.2, U23.15 (B3)
unnamed: J4.26 (from_Bus15), U8.1, U23.11 (B4)
unnamed: J6.3 (CLK_R), J20.1
unnamed: J6.4 (CLK_F), J20.2
unnamed: J7.1, U16.3 (A2)
unnamed: J7.2, U16.2 (A1)
unnamed: J7.3, U16.1 (A0)
unnamed: J8.1, U17.3 (A2)
unnamed: J8.2, U17.2 (A1)
unnamed: J8.3, U17.1 (A0)
unnamed: J9.1, U18.19 (1Q), U20.2 (A1), U21.2 (A1)
unnamed: J9.2, U18.18 (2Q), U20.3 (A2), U21.3 (A2)
unnamed: J9.3, U18.17 (3Q), U20.4 (A3), U21.4 (A3)
unnamed: J9.4, U18.16 (4Q), U20.5 (A4), U21.5 (A4)
unnamed: J9.5, U18.15 (5Q), U20.6 (A5), U21.6 (A5)
unnamed: J9.6, U18.14 (6Q), U20.7 (A6), U21.7 (A6)
unnamed: J9.7, U18.13 (7Q), U20.8 (A7), U21.8 (A7)
unnamed: J9.8, U18.12 (8Q), U20.9 (A8), U21.9 (A8)
unnamed: J9.9, U22.19 (1Q), U25.2 (A1), U26.2 (A1)
unnamed: J9.10, U22.18 (2Q), U25.3 (A2), U26.3 (A2)
unnamed: J9.11, U22.17 (3Q), U25.4 (A3), U26.4 (A3)
unnamed: J9.12, U22.16 (4Q), U25.5 (A4), U26.5 (A4)
unnamed: J9.13, U22.15 (5Q), U25.6 (A5), U26.6 (A5)
unnamed: J9.14, U22.14 (6Q), U25.7 (A6), U26.7 (A6)
unnamed: J9.15, U22.13 (7Q), U25.8 (A7), U26.8 (A7)
unnamed: J9.16, U22.12 (8Q), U25.9 (A8), U26.9 (A8)
unnamed: J10.1, U7.12 (8Q)
unnamed: J10.2, U7.13 (7Q)
unnamed: J10.3, U7.14 (6Q)
unnamed: J10.4, U7.15 (5Q)
unnamed: J10.5, U7.16 (4Q)
unnamed: J10.6, U7.17 (3Q)
unnamed: J10.7, U7.18 (2Q)
unnamed: J10.8, U7.19 (1Q)
unnamed: J10.9, U12.12 (8Q)
unnamed: J10.10, U12.13 (7Q)
unnamed: J10.11, U12.14 (6Q)
unnamed: J10.12, U12.15 (5Q)
unnamed: J10.13, U12.16 (4Q)
unnamed: J10.14, U12.17 (3Q)
unnamed: J10.15, U12.18 (2Q)
unnamed: J10.16, U12.19 (1Q)
unnamed: J11.1, U63.2 (A1)
unnamed: J11.2, U63.3 (A2)
unnamed: J11.3, U63.4 (A3)
unnamed: J11.4, U63.5 (A4)
unnamed: J11.5, U63.6 (A5)
unnamed: J11.6, U63.7 (A6)
unnamed: J11.7, U63.8 (A7)
unnamed: J11.8, U63.9 (A8)
unnamed: J11.9, U67.2 (A1)
unnamed: J11.10, U67.3 (A2)
unnamed: J11.11, U67.4 (A3)
unnamed: J11.12, U67.5 (A4)
unnamed: J11.13, U67.6 (A5)
unnamed: J11.14, U67.7 (A6)
unnamed: J11.15, U67.8 (A7)
unnamed: J11.16, U67.9 (A8)
unnamed: J12.1, U60.19 (1Q), U61.2 (A1), U62.2 (A1)
unnamed: J12.2, U60.18 (2Q), U61.3 (A2), U62.3 (A2)
unnamed: J12.3, U60.17 (3Q), U61.4 (A3), U62.4 (A3)
unnamed: J12.4, U60.16 (4Q), U61.5 (A4), U62.5 (A4)
unnamed: J12.5, U60.15 (5Q), U61.6 (A5), U62.6 (A5)
unnamed: J12.6, U60.14 (6Q), U61.7 (A6), U62.7 (A6)
unnamed: J12.7, U60.13 (7Q), U61.8 (A7), U62.8 (A7)
unnamed: J12.8, U60.12 (8Q), U61.9 (A8), U62.9 (A8)
unnamed: J12.9, U64.19 (1Q), U65.2 (A1), U66.2 (A1)
unnamed: J12.10, U64.18 (2Q), U65.3 (A2), U66.3 (A2)
unnamed: J12.11, U64.17 (3Q), U65.4 (A3), U66.4 (A3)
unnamed: J12.12, U64.16 (4Q), U65.5 (A4), U66.5 (A4)
unnamed: J12.13, U64.15 (5Q), U65.6 (A5), U66.6 (A5)
unnamed: J12.14, U64.14 (6Q), U65.7 (A6), U66.7 (A6)
unnamed: J12.15, U64.13 (7Q), U65.8 (A7), U66.8 (A7)
unnamed: J12.16, U65.9 (A8), U66.9 (A8)
unnamed: J13.1, J15.7, U22.9 (8D), U33.9 (8D), U39.9 (8D), U45.9 (8D), U51.9 (8D), U57.9 (8D)
unnamed: J13.2, U22.8 (7D), U33.8 (7D), U39.8 (7D), U45.8 (7D), U51.8 (7D), U57.8 (7D), U64.8 (7D)
unnamed: J13.3, U22.7 (6D), U33.7 (6D), U39.7 (6D), U45.7 (6D), U51.7 (6D), U57.7 (6D), U64.7 (6D)
unnamed: J13.4, U22.6 (5D), U33.6 (5D), U39.6 (5D), U45.6 (5D), U51.6 (5D), U57.6 (5D), U64.6 (5D)
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
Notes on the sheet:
FLAG
ZERO

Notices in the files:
circets/Activation_Module/Activation_Module/Activation_Module.kicad_pcb:
Licens: Apache License 2.0
circets/Dual_Register/dual_register/dual_register.kicad_pcb:
License: Apache License 2.0
